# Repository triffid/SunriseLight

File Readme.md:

# Sunrise Light

A bluetooth-controlled RGB LED strip controller with battery backup, including time/location based color temperature control ala F.lux/Redshift/etc and party mode.

[Schematic (pdf)](http://triffid-hunter.no-ip.info/Sunrise.pdf)

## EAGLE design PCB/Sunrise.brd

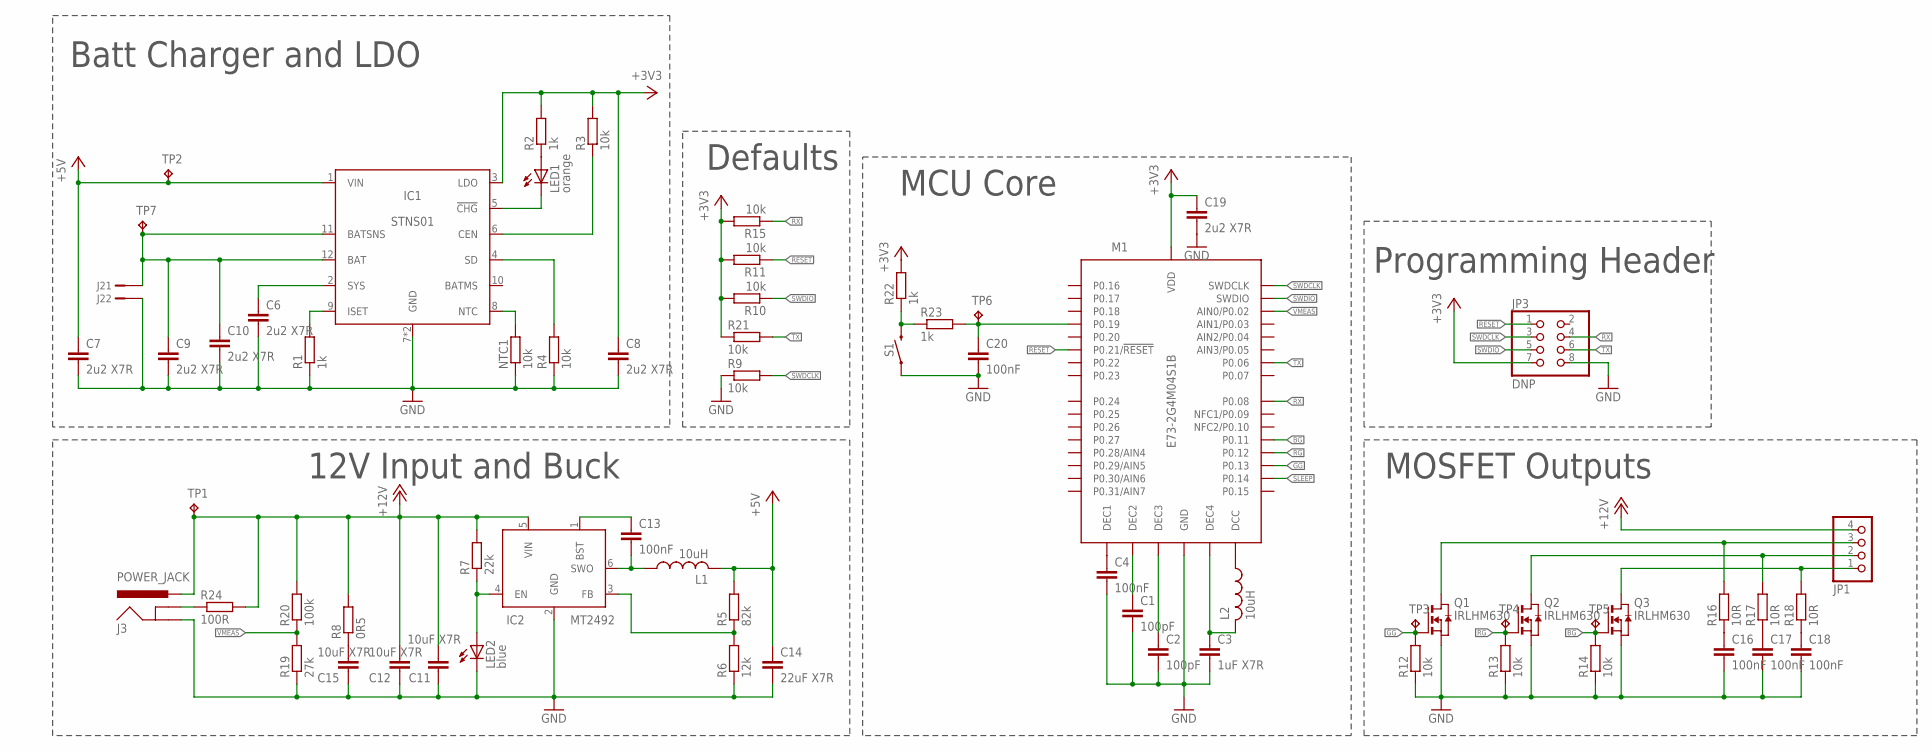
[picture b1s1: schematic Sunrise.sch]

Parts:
C1, C2: 100pF; C0402K
C3: 1uF X7R; C0603K
C4, C13, C16, C17, C18, C20: 100nF; C0402K
C6, C7, C8, C9, C10, C19: 2u2 X7R; C0603K
C11, C12, C15: 10uF X7R; C1206K
C14: 22uF X7R; C1206K
IC1: STNS01; DFN12L-3MM; MPN STNS01
IC2: MT2492; SOT23-6; MPN MT2492
J2: B2B-PH-K-S; MPN B2B-PH-K-S
J3: POWER_JACK; POWER_JACK_PTH
JP1: PINHD-1X4/90; 1X04/90
JP3: DNP; 2X04
L1: 10uH; 2020-5050; MPN LQH5BPN100MT0
L2: 10uH; 0603-1608
LED1: orange; CHIP-LED0603
LED2: blue; CHIP-LED0603
M1: E73-2G4M04S1B; E73-2GM404S; MPN E7302G4M04S1B
NTC1: 10k; R0402
Q1, Q2, Q3: IRLHM630; MLP8-33; MPN IRLHM630TRPbF
R1, R2, R22, R23: 1k; R0402
R3, R4, R9, R10, R11, R12, R13, R14, R15, R21: 10k; R0402
R5: 82k; R0402
R6: 12k; R0402
R7: 22k; R0402
R8: 0R5; R0402
R16, R17, R18: 10R; R0402
R19: 27k; R0402
R20: 100k; R0402
R24: 100R; R0402
S1: MOMENTARY-SWITCH-SPST-SMD-5.2MM; TACTILE_SWITCH_SMD_5.2MM
TP1, TP2, TP3, TP4, TP5, TP6, TP7: TPTP10R; TP10R

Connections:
+3V3: C8.1, C19.1, IC1.3 (LDO), JP3.7, M1.16 (VDD), R2.2, R3.2, R10.2, R11.2, R15.2, R21.1, R22.2
+5V: C7.1, C14.1, IC1.1 (VIN), L1.2, R5.2, TP2.TP
+12V: C11.1, C12.1, IC2.5 (VIN), J3.PWR, JP1.4, R7.2, R8.2, R20.2, R24.2, TP1.TP
BG: M1.26 (P0.11), Q3.GATE (G), R14.2, TP5.TP
GG: M1.28 (P0.13), Q1.GATE (G), R12.2, TP3.TP
GND: C1.2, C2.2, C3.2, C4.2, C6.2, C7.2, C8.2, C9.2, C10.2, C11.2, C12.2, C14.2, C15.2, C16.2, C17.2, C18.2, C19.2, C20.2, IC1.7 (GND), IC1.PAD (GND), IC2.2 (GND), J2.2, J3.GND, JP3.8, LED2.C, M1.0 (GND), M1.1 (GND), M1.2 (GND), M1.15 (GND), M1.42 (GND), M1.43 (GND), NTC1.1, Q1.S1 (S), Q1.S2 (S), Q1.S3 (S), Q2.S1 (S), Q2.S2 (S), Q2.S3 (S), Q3.S1 (S), Q3.S2 (S), Q3.S3 (S), R1.1, R4.1, R6.1, R9.1, R12.1, R13.1, R14.1, R19.1, S1.1
unnamed: C4.1, M1.14 (DEC1)
unnamed: C1.1, M1.3 (DEC2)
unnamed: C3.1, L2.2, M1.12 (DEC4)
unnamed: C2.1, M1.4 (DEC3)
unnamed: L2.1, M1.13 (DCC)
unnamed: C9.1, C10.1, IC1.11 (BATSNS), IC1.12 (BAT), J2.1, TP7.TP
unnamed: C6.1, IC1.2 (SYS)
unnamed: IC1.8 (NTC), NTC1.2
unnamed: IC1.9 (ISET), R1.2
unnamed: LED1.A, R2.1
unnamed: IC1.5 (!CHG), LED1.C
unnamed: IC1.6 (CEN), R3.1
unnamed: IC1.4 (SD), R4.2
unnamed: C15.1, R8.1
unnamed: JP1.1, Q3.D1 (D), Q3.D2 (D), Q3.D3 (D), Q3.D4 (D), Q3.DRAIN0 (D), R18.2
unnamed: JP1.2, Q2.D1 (D), Q2.D2 (D), Q2.D3 (D), Q2.D4 (D), Q2.DRAIN0 (D), R17.2
unnamed: C13.1, IC2.1 (BST)
unnamed: IC2.3 (FB), R5.1, R6.2
unnamed: JP1.3, Q1.D1 (D), Q1.D2 (D), Q1.D3 (D), Q1.D4 (D), Q1.DRAIN0 (D), R16.2
unnamed: C13.2, IC2.6 (SWO), L1.1
unnamed: IC2.4 (EN), LED2.A, R7.1
unnamed: C16.1, R16.1
unnamed: C17.1, R17.1
unnamed: C18.1, R18.1
unnamed: R22.1, R23.1, S1.3 (2)
unnamed: C20.1, M1.34 (P0.19), R23.2, TP6.TP
unnamed: J3.GNDBREAK, R24.1
RESET: JP3.1, M1.36 (P0.21/!RESET), R11.1
RG: M1.27 (P0.12), Q2.GATE (G), R13.2, TP4.TP
RX: JP3.4, M1.23 (P0.08), R15.1
SLEEP: M1.29 (P0.14)
SWDCLK: JP3.3, M1.37 (SWDCLK), R9.2
SWDIO: JP3.5, M1.38 (SWDIO), R10.1
TX: JP3.6, M1.21 (P0.06), R21.2
VMEAS: M1.17 (AIN0/P0.02), R19.2, R20.1

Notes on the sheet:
12V Input and Buck
Batt Charger and LDO
MCU Core
Defaults
Programming Header
MOSFET Outputs

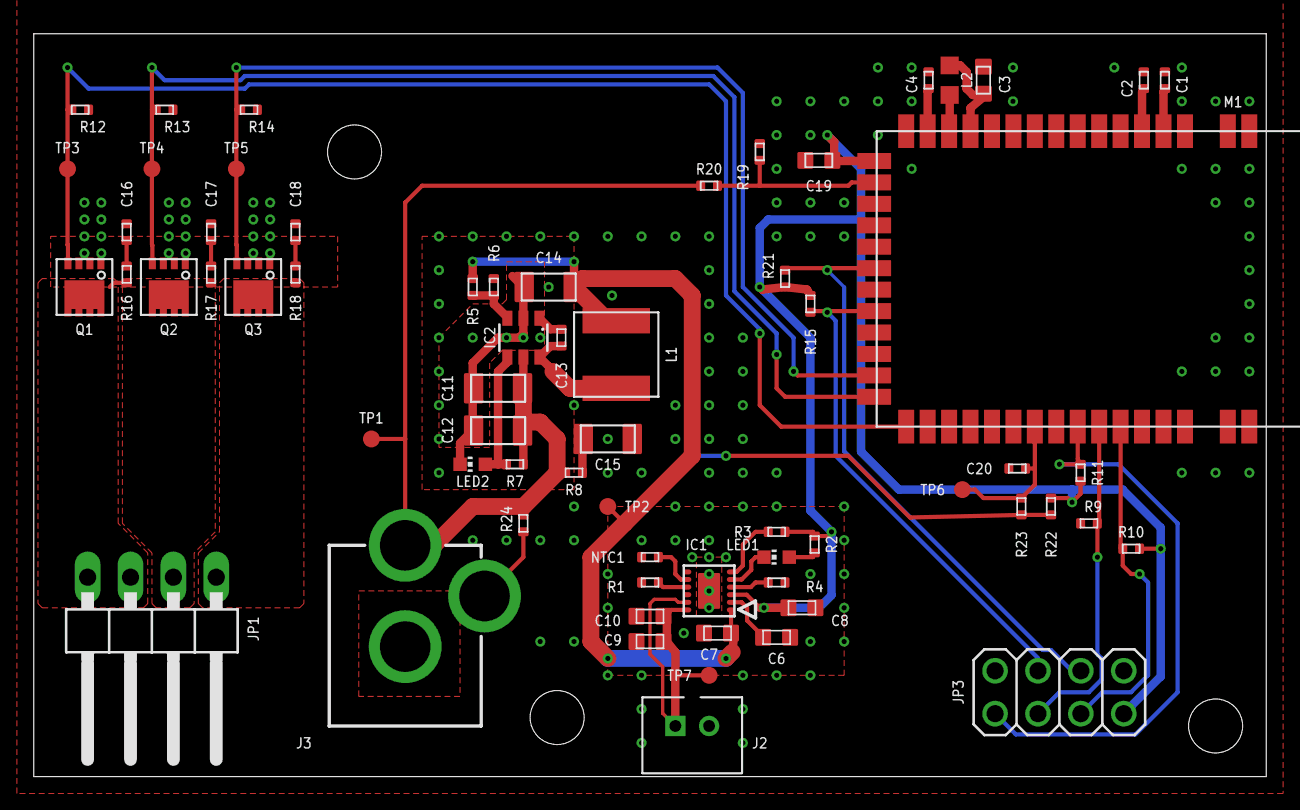
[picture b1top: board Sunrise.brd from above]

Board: 2 copper layers, 73.0 x 44.0 mm, 66 parts (1 on the bottom side), 40 nets.

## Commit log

2018-12-06 Initial commit, first rev of sunrise light
2018-12-14 Ignore a bunch of output files
2018-12-14 Move PCB into a subdir to make room for firmware
2018-12-17 Firmware starting to come together, still needs a ton of work
2018-12-17 simpler ΣΔ that doesn't depend on reading previous GPIO
2018-12-17 Bump timer freq, stop calculating times per second
2018-12-18 Pull stuf from RedShift, seems to work!
2018-12-18 Move BLE to separate file to try and clean main
2018-12-21 Bunch of stuff sorta working, crude beginning of custom service
2018-12-21 Add Bootloader incl. public key. Private key not in repo for reasons
2018-12-21 PCB: Clean schematic, move values on board around a bit, no actual connectivity or component changes
2018-12-21 Continuously report no power and current time while 12v input is absent, for debugging
2018-12-21 Change line endings to UNIX
2018-12-21 Ignore Bootloader build dir
2018-12-21 BLE characteristic actually updates current time now!
2018-12-24 Start encapsuatling ble characteristic setup, doesn't immediately crash!
2018-12-25 Add our own custom redshift location provider that can be updated.
    Update redshift colours immediately upon poweron event rather than waiting for timer tick.
    Add exponent field to presentation format descriptor
    Assign UUIDs via enum
    Dispatch BLE write events via dispatch receiver info
2018-12-25 Add an enum of all BLE units for convenience; auto-generated from JSON list in https://www.bluetooth.com/specifications/assigned-numbers/units to avoid errors
2018-12-25 Condense characteristic adding to a single standalone macro, add characteristics for day/night color temperature and brightness
2018-12-26 Add manual, party, and off modes, controllable via BLE
2018-12-27 Fix bug where location wasn't being fed to solar_elevation for some reason
2019-01-02 Check more carefully whether to start advertising, shrink hook table of state receivers to match usage, a bit less logging, tell DFU that it can use bonds
2019-01-02 PCB: Minor update to NRF52 module; specify a package variant and expand its description
2019-01-07 Turn LEDs off every clock tick while in soft-off, use appropriate header for bsp_board_leds_off()
2019-10-10 Firmware: fix compile errors with NRF5_SDK_15.3.0
2019-10-10 Relabel red/green/blue channels to match common RGB strips
2019-10-10 gitignore: ignore JPEGs
2019-10-26 Add readme
2021-02-14 Firmware/Makefile: consolidate build flags
2021-02-14 Update some footprints, add attributes to several components

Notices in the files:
parts and their libraries:
SparkFun-Connectors: Licensing: Creative Commons ShareAlike 4.0 International - https://creativecommons.org/licenses/by-sa/4.0
